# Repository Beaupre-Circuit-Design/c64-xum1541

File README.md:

# C64-XUM1541

# Introduction

This project is a collections of 3 subprojects, XUM1541, an OpenCBM compatible interface, a VIA adapter to add a parallel interface to a 1541 (SpeedDos and XUM1541 Compatible) and a C64 User Port adapter for the paralle interface (SpeedDos compatible).

If the only thing you need is to backup and restore your floppies via a PC, only the XUM1541 is needed, with the optional VIA adapter if you want to make things a bit faster. The User Port adapter require a ROM upgrade for the C64 and the 1541 (which can be done with a ROM adapter like the [23xx Adapter](https://github.com/Beaupre-Circuit-Design/23xx-Adapter).

|Module           |PC |C64|SpeedDos|Description                                            |
|-----------------|---|---|--------|-------------------------------------------------------|
|[XUM1541](xum1541/)|Yes|N/A|N/A|Module for backing up and restoring floppies disk to PC|
|[VIA Adapter](xum1541-parallel-adapter/)|Optional|N/A|Required|Parallel interface for the 1541 disk drive|
|[User Port Adapter](xum1541-via-adapter)|N/A|N/A|Required|Parallel interface for the C64 user port|
|[23xx Adapter](https://github.com/Beaupre-Circuit-Design/23xx-Adapter)|N/A|N/A|Required|ROM adapter needed to install the SpeedDos Rom, needed to be done on both the C64 and the 1541|

See each project for build details.

# Licence

This work is licensed under the Creative Commons Attribution-NonCommercial-ShareAlike 4.0 International License. To view a copy of this license, visit http://creativecommons.org/licenses/by-nc-sa/4.0/ or send a letter to Creative Commons, PO Box 1866, Mountain View, CA 94042, USA.

# Revision History

|Revision  |Description                    |
|:--------:|-------------------------------|
|1.0       |Initial prototype              |
|2.0       |Add bank switching header      |

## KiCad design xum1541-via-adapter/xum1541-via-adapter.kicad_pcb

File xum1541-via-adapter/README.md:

# XUM1541 VIA Adapter

# Introduction

A SpeedDos compatible VIA Adapter for the 1541 disk drive to enable parallel communication.

# Components and assembly

Component selection isn't terribly critical, whathever you have in hand that fit the values will probably work just fine. Values for the led resistors will drive them at around 18ma which may be quite bright, increase the values if it's the case.

As alway, when assembling, start with the smallest components and grow in size as you go.

|Qty|Ref|Value|Description|
|---|---|-----|-----------|
|2|U1A|Conn_01x20|20 pin 2.54mm Round Male Connector Single Row|
|1|U1B|Conn_02x06_Odd_Even|Shrouded Square Pins 2.5mm 6mm 2x6 Pin Headers Righ Angle|

# Licence

This work is licensed under the Creative Commons Attribution-NonCommercial-ShareAlike 4.0 International License. To view a copy of this license, visit http://creativecommons.org/licenses/by-nc-sa/4.0/ or send a letter to Creative Commons, PO Box 1866, Mountain View, CA 94042, USA.

# Revision History

|Revision  |Description                    |
|:--------:|-------------------------------|
|1.0       |Initial prototype              |

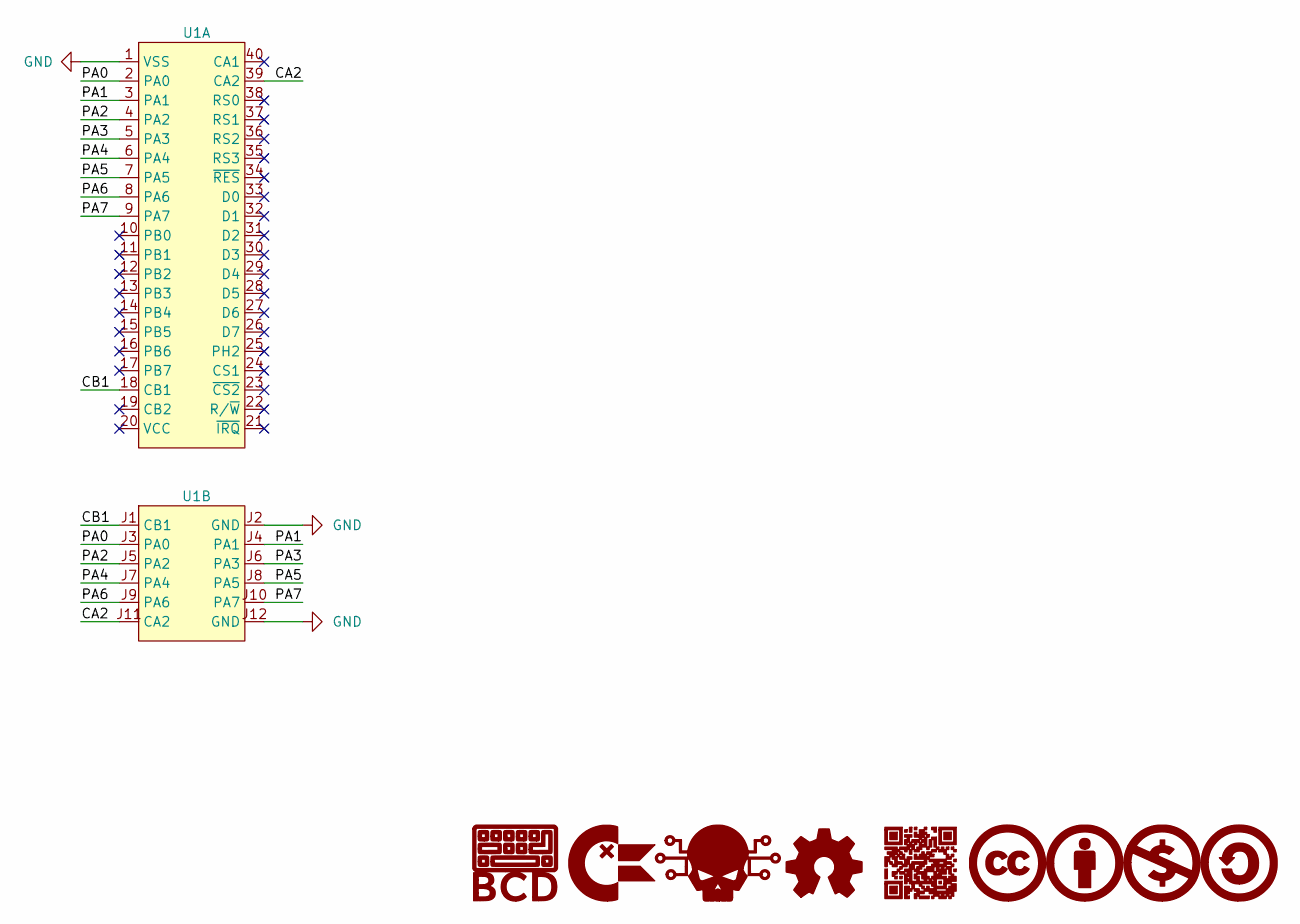
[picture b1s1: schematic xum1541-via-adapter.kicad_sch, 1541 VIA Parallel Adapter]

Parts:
G1: BCD_Logo; BCD_Logo_5mm
G2: ChickenLips; ChickenLips_2.5mm
G3: Skull; Skull_2.5mm
G4: OpenSource_Hardware; Open_Source_Hardware_2.5mm
G5: CreativeCommons; CreativeCommons_2.5mm
G6: CreativeCommons_Attribution; CreativeCommons_Attribution_2.5mm
G7: CreativeCommons_NonCommercial; CreativeCommons_NonCommercial_2.5mm
G8: CreativeCommons_ShareAlike; CreativeCommons_ShareAlike_2.5mm
G9: BDC_QR; BDC_QR_5mm
U1: MCS6522; MCS6522 Adapter

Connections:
/CA2: U1.39 (CA2), U1.J11 (CA2)
/CB1: U1.18 (CB1), U1.J1 (CB1)
/PA0: U1.2 (PA0), U1.J3 (PA0)
/PA1: U1.3 (PA1), U1.J4 (PA1)
/PA2: U1.4 (PA2), U1.J5 (PA2)
/PA3: U1.5 (PA3), U1.J6 (PA3)
/PA4: U1.6 (PA4), U1.J7 (PA4)
/PA5: U1.7 (PA5), U1.J8 (PA5)
/PA6: U1.8 (PA6), U1.J9 (PA6)
/PA7: U1.9 (PA7), U1.J10 (PA7)
GND: U1.1 (VSS), U1.J2 (GND), U1.J12 (GND)

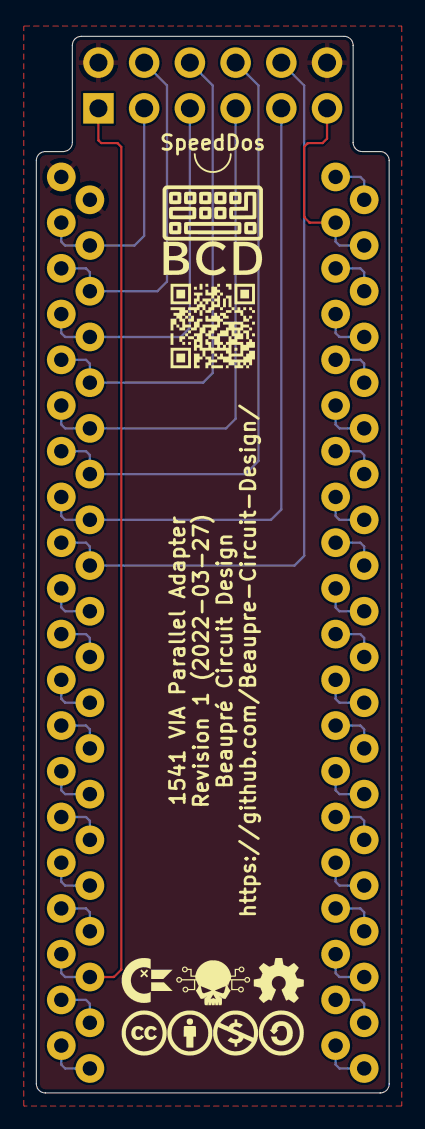
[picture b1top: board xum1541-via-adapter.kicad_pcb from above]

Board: 2 copper layers, 19.6 x 58.7 mm, 10 parts (0 on the bottom side), 11 nets.

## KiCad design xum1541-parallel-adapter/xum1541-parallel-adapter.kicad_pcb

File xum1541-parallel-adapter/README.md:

# XUM1541 Parallel Adapter

# Introduction

A SpeedDos compatible interface for the 1541 disk drive to enable parallel communication.

# Components and assembly

Component selection isn't terribly critical, whathever you have in hand that fit the values will probably work just fine. Values for the led resistors will drive them at around 18ma which may be quite bright, increase the values if it's the case.

As alway, when assembling, start with the smallest components and grow in size as you go.

|Qty|Ref|Value|Description|
|---|---|-----|-----------|
|1|D1|Red Led|Light Emitting Diodes Red Diffused 5mm 20mA/1.9V|
|1|R1|180Ω|Resistors 180Ω Axial Leaded Through Hole|
|1|SW1|SW_Push|Micro-Switch 6x6mm|
|1|UP1|C64 User Port|24 Pins 805 Series 3.96mm Pitch PCB Slot Solder Card Edge Connector|

# Licence

This work is licensed under the Creative Commons Attribution-NonCommercial-ShareAlike 4.0 International License. To view a copy of this license, visit http://creativecommons.org/licenses/by-nc-sa/4.0/ or send a letter to Creative Commons, PO Box 1866, Mountain View, CA 94042, USA.

# Revision History

|Revision  |Description                    |
|:--------:|-------------------------------|
|1.0       |Initial prototype              |

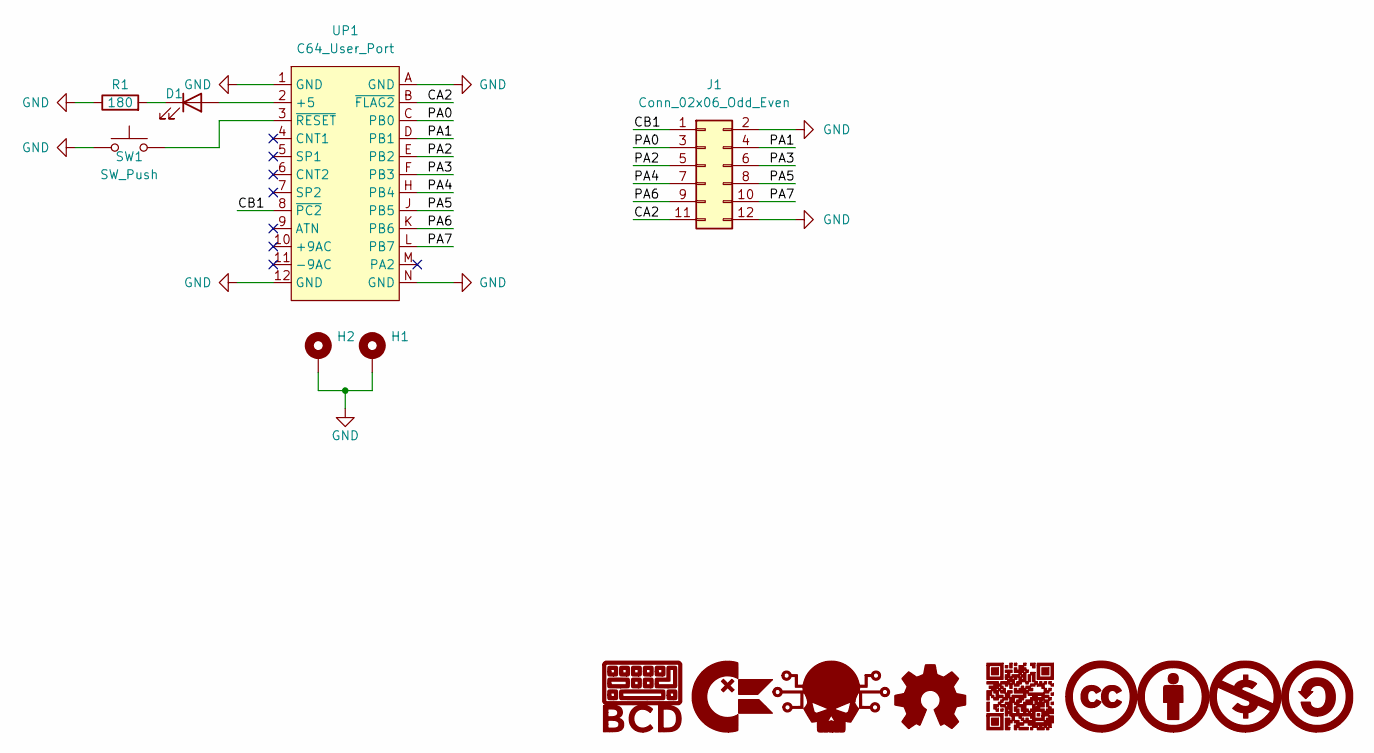
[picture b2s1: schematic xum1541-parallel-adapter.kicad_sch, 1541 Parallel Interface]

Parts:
D1: LED; LED_D5.0mm; Mfr.Part L-513ID; LCSC C2895168
G1: BCD_Logo; BCD_Logo_5mm
G2: ChickenLips; ChickenLips_2.5mm
G3: Skull; Skull_2.5mm
G4: OpenSource_Hardware; Open_Source_Hardware_2.5mm
G5: CreativeCommons; CreativeCommons_2.5mm
G6: CreativeCommons_Attribution; CreativeCommons_Attribution_2.5mm
G7: CreativeCommons_NonCommercial; CreativeCommons_NonCommercial_2.5mm
G8: CreativeCommons_ShareAlike; CreativeCommons_ShareAlike_2.5mm
G9: BDC_QR; BDC_QR_5mm
H1, H2: MountingHole_Pad; MountingHole_3.2mm_M3_Pad
J1: Conn_02x06_Odd_Even; PinHeader_2x06_P2.54mm_Horizontal; Mfr.Part PZ254R-12-12P; LCSC C492434
R1: 180; R_Axial_DIN0207_L6.3mm_D2.5mm_P10.16mm_Horizontal; Mfr.Part MFR0W4F1800A50; LCSC C58665
SW1: SW_Push; SW_PUSH_6mm_H4.3mm
UP1: C64_User_Port; C64 User Port

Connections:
/CA2: J1.11, UP1.B (~FLAG2)
/CB1: J1.1, UP1.8 (~PC2)
/PA0: J1.3, UP1.C (PB0)
/PA1: J1.4, UP1.D (PB1)
/PA2: J1.5, UP1.E (PB2)
/PA3: J1.6, UP1.F (PB3)
/PA4: J1.7, UP1.H (PB4)
/PA5: J1.8, UP1.J (PB5)
/PA6: J1.9, UP1.K (PB6)
/PA7: J1.10, UP1.L (PB7)
GND: H1.1, H2.1, J1.2, J1.12, R1.1, SW1.1, UP1.1 (GND), UP1.12 (GND), UP1.A (GND), UP1.N (GND)
unnamed: D1.1 (K), R1.2
unnamed: D1.2 (A), UP1.2 (+5)
unnamed: SW1.2, UP1.3 (~RESET)

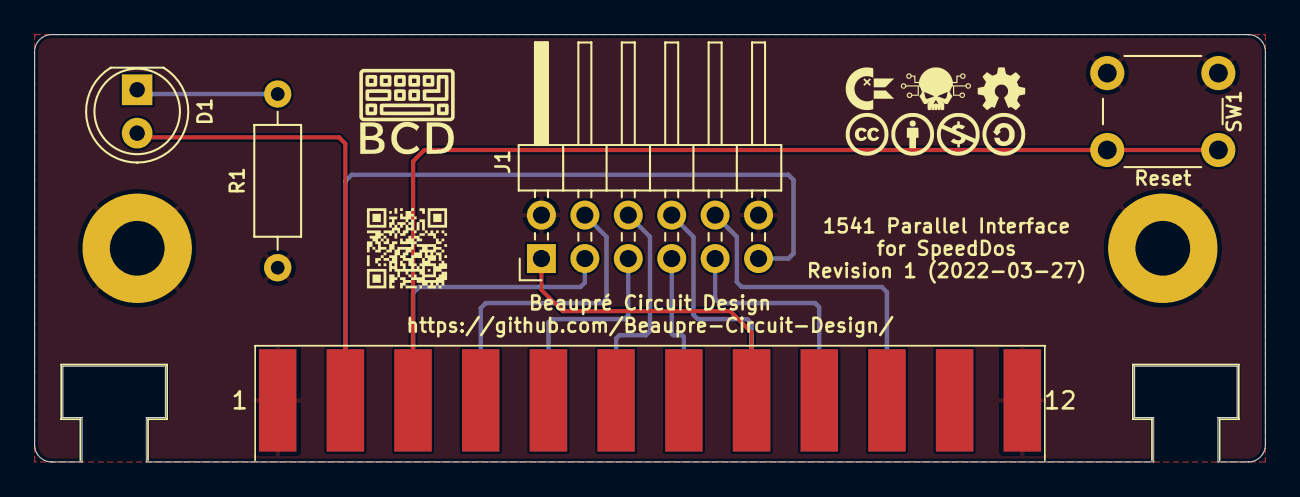
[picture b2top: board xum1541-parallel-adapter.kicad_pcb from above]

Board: 2 copper layers, 72.0 x 25.0 mm, 16 parts (0 on the bottom side), 14 nets.

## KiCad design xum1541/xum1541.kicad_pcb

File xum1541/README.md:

# XUM1541

# Introduction

An OpenCBM compatible interface for the 1541 disk drive that can be used to backup and restore floppies.

# Components and assembly

Component selection isn't terribly critical, whathever you have in hand that fit the values will probably work just fine. Values for the led resistors will drive them at around 18ma which may be quite bright, increase the values if it's the case. R1 to R5 can be anything between 1KΩ and 100KΩ. The decoupling capacitor C1 should be at least 10v or more.

As alway, when assembling, start with the smallest components (resistor and capacitor) and grow in size as you go.

|Qty|Ref|Value|Description|
|---|---|-----|-----------|
|1|C1|100nF|Ceramic Disc Capacitors 100nF 2.54mm Radial Leads (10v or more)|
|1|D1|Red Led|Light Emitting Diodes Red Diffused 5mm 20mA/1.9V|
|1|D2|Green Led|Light Emitting Diodes Green Diffused 5mm 20mA/2.2V|
|1|J1|Conn_02x06_Odd_Even|Pin Headers Righ Angle 2.54mm 2x6 Pin|
|1|J2|DIN-45322|6 pin Female DIN connector (240°) DIN 45322/60130-9 IEC-17|
|5|R1-R5|100kΩ|Resistors 100kΩ Axial Leaded Through Hole|
|1|R6|180Ω|Resistors 180Ω Axial Leaded Through Hole|
|1|R7|150Ω|Resistors 150Ω Axial Leaded Through Hole|
|1|SW1|SW_Push|Micro-Switch 6x6mm|
|1|U1|Arduino_Pro_Micro|SparkFun Arduino Pro Micro ATmega32U4|
|1|U2|74LS06|DIP-14 Inverters|

## Firmware

The firmware source code is available in the OpenCBM repository if you want to compile it yourself but since the code is stable and mature, it is not really needed and we can use a precompiled version. At the time of release, the current version is V08. 

Theses instructions are for Windows, but all the needed softwares are available for about any other platforms.

|Software|Local Link|Official Repository|
|--------|:----------:|:-----------:|
|Firmware|[xum1541-PROMICRO_7406-v08.hex](Firmware/xum1541-PROMICRO_7406-v08.hex)|[OpenCBM xum1541 Firmware](https://github.com/zyonee/opencbm/tree/master/xum1541)|
|WinAVR|N/A|[WinAVR Latest Release](https://sourceforge.net/projects/winavr/files/latest/download)|
|Zadig|N/A|[Zadig Latest Release](https://zadig.akeo.ie/)|
|OpenCBM|N/A|[OpenCBM Latest Release](https://spiro.trikaliotis.net/opencbm#download)|

Install WinAVR and open Device Manager, then connect the Arduino Pro Micro. A new Serial Port should appear after a few seconds.

This is the monitor serial port, but not the one we want, to put the Arduino into programming mode, reset it twice, you should see the Com Port number change, which tell you that we are in Firmware Update mode.

The Arduino will stay in this mode for about 8 seconds then revert back to the monitor serial port mode. So you need to be a little bit fast. First, note the Com Port number when the device is in Firmware Update mode (In this case, COM4), then open a command prompt and go to the bin directory of WinAVR. Once there, enter the following command but do not press enter (Adjust the path and filename of the firmware as needed):

~~~
avrdude -p m32u4 -c avr109 -P com4 -U flash:w:xum1541-PROMICRO_7406-v08.hex
~~~

Then, reset the Arduino twice to put it in programming mode and press enter. If everything goes well you should get a result like this:

~~~
C:\WinAVR-20100110\bin>avrdude -p m32u4 -c avr109 -P com4 -U flash:w:xum1541-PROMICRO_7406-v08.hex

Connecting to programmer: .
Found programmer: Id = "CATERIN"; type = S
    Software Version = 1.0; No Hardware Version given.
Programmer supports auto addr increment.
Programmer supports buffered memory access with buffersize=128 bytes.

Programmer supports the following devices:
    Device code: 0x44

avrdude: AVR device initialized and ready to accept instructions

Reading | ################################################## | 100% 0.00s

avrdude: Device signature = 0x1e9587
avrdude: NOTE: FLASH memory has been specified, an erase cycle will be performed
         To disable this feature, specify the -D option.
avrdude: erasing chip
avrdude: reading input file "xum1541-PROMICRO_7406-v08.hex"
avrdude: input file xum1541-PROMICRO_7406-v08.hex auto detected as Intel Hex
avrdude: writing flash (9026 bytes):

Writing | ################################################## | 100% 1.29s

avrdude: 9026 bytes of flash written
avrdude: verifying flash memory against xum1541-PROMICRO_7406-v08.hex:
avrdude: load data flash data from input file xum1541-PROMICRO_7406-v08.hex:
avrdude: input file xum1541-PROMICRO_7406-v08.hex auto detected as Intel Hex
avrdude: input file xum1541-PROMICRO_7406-v08.hex contains 9026 bytes
avrdude: reading on-chip flash data:

Reading | ################################################## | 100% 0.41s

avrdude: verifying ...
avrdude: 9026 bytes of flash verified

avrdude: safemode: Fuses OK

avrdude done.  Thank you.

C:\WinAVR-20100110\bin>
~~~

The Arduino will reset after the Firmware Upload and a new device should appear in device manager:

## Driver installation

Next, we need to install the driver for the new device, start **Zadig** and select the **xum1541 floppy adapter (PROMICRO_7406)** device, next change the driver to **libusp-win32**, finally click **Install Driver** and wait for the confirmation message.

## OpenCBM Installation

Unzip OpenCBM into a temporary directory and open a **Command Prompt** in **Administrator** mode, switch to the temporary OpenCBM directory and type the following command:

~~~
install.cmd xum1541
~~~

Install will start, check for a previous installation and advice that it will request elevated privileges, press any key to start installation or CTRL-C to abort.

~~~
find: /i: No such file or directory
OpenCBM installation script
===========================

Elevating privileges in order to install OpenCBM.
Please grant the rights on the UAC prompt,
or I will not be able to continue

Your installation will continue in another window.
Press any key to continue . . .
~~~

Another window will open and installation will continue, when it ask to install drivers, answer no since they have already been install.

~~~
Continuing...
24 File(s) copied
5 File(s) copied
2 File(s) copied
3 File(s) copied
Working directory = 'C:\Program Files\opencbm\',
system  directory = 'C:\Windows\system32\',
driver  directory = 'C:\Windows\system32\DRIVERS\'.
Using plugin: 'xum1541' with filename 'opencbm-xum1541.dll'.
++++ Install: 'xum1541' with filename 'opencbm-xum1541.dll'.
Copying '.\opencbm-xum1541.dll' to 'C:\Windows\system32\opencbm-xum1541.dll'

=================================================
=== OpenCBM v0.4.99.104 for  xum1541
=== installation done
===
=== Add C:\Program Files\opencbm to your PATH to use the command line tools there.
=================================================

I could install the necessary USB drivers if you like.
If you want this, then please
1. attach your device, and then
2. answer the following question with "y", without parenthesis:

Do you want me to install the necessary USB drivers for you? (y/n) n
NO.

That's it, I am finished.
Press any key to continue . . .
~~~

## Testing

First, test without connecting anything, open an OpenCBM Shell  and type the following command:

~~~
cbmctrl detect
~~~

You should get the following error:

~~~
C:\Users\xum1541>cbmctrl detect
error: no xum1541 device found
An error occurred opening OpenCBM, aborting...

C:\Users\xum1541>
~~~

Next, connect the XUM1541 but do not connect a drive to it and try the command again, this time your should not see any output. This confirm that the XUM1541 is detected and working correctly.

~~~
C:\Users\xum1541>cbmctrl detect

C:\Users\xum1541>
~~~

Finally, disconnect the XUM1541 from the computer and make sure the 1541 is powered off, connect the 1541 to the XUM1541 with the IEC Cable, connect the XUM1541 to the computer and finally turn on the 1541. You may now try the command again, and this time you should see the device ID and model of the connected disk drive.

~~~
C:\Users\xum1541>cbmctrl detect
 8: 1541-II

C:\Users\xum1541>
~~~

## Basic OpenCBM commands

This is definitly not an exaustive guide, but just a few commands to test and do basic tasks.

### Reading disk directory

Reading the disk directory can be done with the **cbmctrl dir \<DISKID\>** command:

~~~
C:\Users\xum1541>cbmctrl dir 8
0 ."test/demo  1/85 " 84 2a
14   "how to use"       prg
8    "how part two"     prg
7    "how part three"   prg
4    "vic-20 wedge"     prg
1    "c-64 wedge"       prg
4    "dos 5.1"          prg
9    "printer test"     prg
6    "disk addr change" prg
12   "view bam"         prg
15   "display t&s"      prg
4    "check disk"       prg
11   "performance test" prg
5    "seq.file.demo"    prg
18   "rel.file.demo"    prg
7    "sd.backup.c16"    prg
7    "sd.backup.plus4"  prg
10   "sd.backup.c64"    prg
7    "print.64.util"    prg
7    "print.c16.util"   prg
7    "print.+4.util"    prg
13   "uni-copy"         prg
30   "c64 basic demo"   prg
35   "+4 basic demo"    prg
8    "load address"     prg
7    "unscratch"        prg
5    "header change"    prg
403 blocks free.
00, ok,00,00

C:\Users\xum1541>
~~~

### Backing up disk to PC or restore to disk from PC

Making backup or restoring a disk can be done with the **d64copy \<SRC\> \<DST\>** command:

Backup disk in drive id **8** to disk image **1541-demo.d64**:
~~~
C:\Users\xum1541>d64copy 8 1541-demo.d64
[Warning] growing image file to 683 blocks
 1: *********************
 2: *********************
 3: *********************
 4: *********************
 5: *********************
 6: *********************
 7: *********************
 8: *********************
 9: *********************
10: *********************
11: *********************
12: *********************
13: *********************
14: *********************
15: *********************
16: *********************
17: *********************
18: *******************
19: *******************
20: *******************
21: *******************
22: *******************
23: *******************
24: *******************
25: ******************
26: ******************
27: ******************
28: ******************
29: ******************
30: ******************
31: *****************
32: *****************
33: *****************
34: *****************
35: *****************       100%   683/683
683 blocks copied.

C:\Users\xum1541>
~~~

Restore disk image **1541-demo.d64** to disk in drive id **8**:

~~~
C:\Users\xum1541>d64copy 1541-demo.d64 8
 1: *********************
 2: *********************
 3: *********************
 4: *********************
 5: *********************
 6: *********************
 7: *********************
 8: *********************
 9: *********************
10: *********************
11: *********************
12: *********************
13: *********************
14: *********************
15: *********************
16: *********************
17: *********************
18: *******************
19: *******************
20: *******************
21: *******************
22: *******************
23: *******************
24: *******************
25: ******************
26: ******************
27: ******************
28: ******************
29: ******************
30: ******************
31: *****************
32: *****************
33: *****************
34: *****************
35: *****************       100%   683/683
683 blocks copied.

C:\Users\xum1541>
~~~

### Format a disk

Format a disk in drive id **8**:

~~~
C:\Users\xum1541>cbmformat 8 XUM1541_FORMAT,01 -c

C:\Users\xum1541>cbmctrl dir 8
0 ."xum1541⌂format  " 01 2a
664 blocks free.
00, ok,00,00

C:\Users\xum1541>
~~~

For more information, see the official [OpenCBM](https://opencbm.trikaliotis.net/) documentation.

# Licence

This work is licensed under the Creative Commons Attribution-NonCommercial-ShareAlike 4.0 International License. To view a copy of this license, visit http://creativecommons.org/licenses/by-nc-sa/4.0/ or send a letter to Creative Commons, PO Box 1866, Mountain View, CA 94042, USA.

# Revision History

|Revision  |Description                    |
|:--------:|-------------------------------|
|1.0       |Initial prototype              |

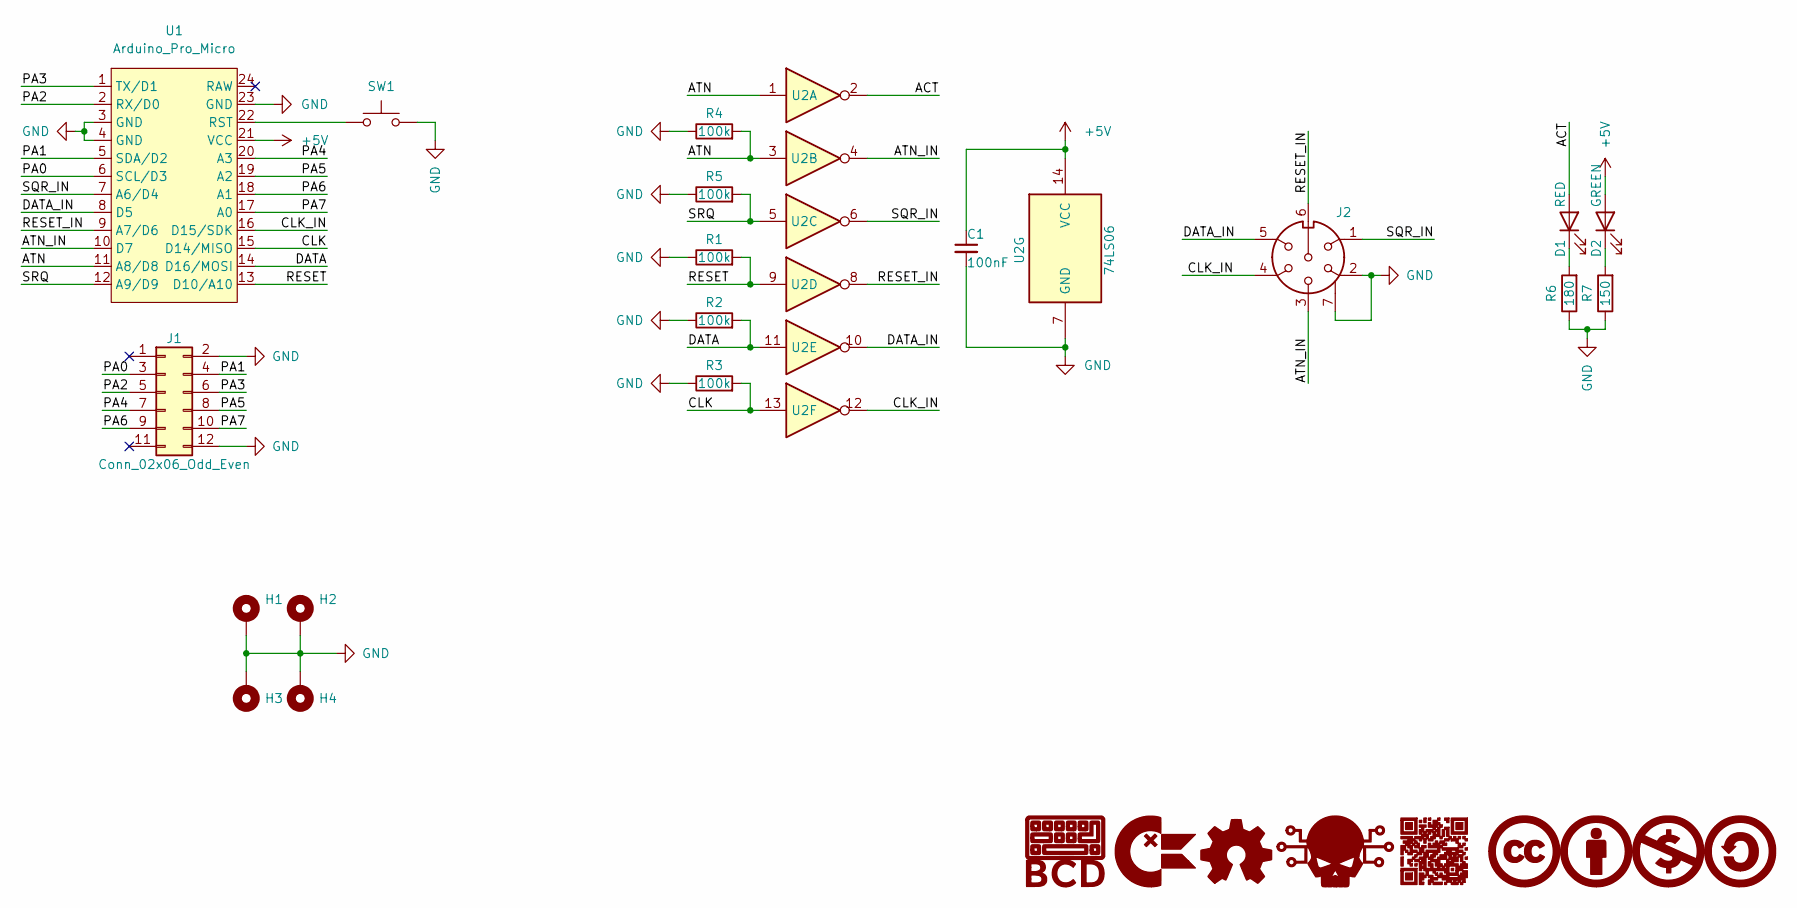
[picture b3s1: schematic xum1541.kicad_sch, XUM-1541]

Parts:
C1: 100nF; C_Disc_D5.0mm_W2.5mm_P2.50mm; Mfr.Part CC1H104ZA1PD3F5P3003; LCSC C353903
D1: RED; LED_D5.0mm; Mfr.Part L-513ID; LCSC C2895168
D2: GREEN; LED_D5.0mm; Mfr.Part L-513GD; LCSC C2895169
G1: BCD_Logo; BCD_Logo_5mm
G2: ChickenLips; ChickenLips_5mm
G3: OpenSource_Hardware; Open_Source_Hardware_5mm
G4: Skull; Skull_5mm
G5: CreativeCommons; CreativeCommons_5mm
G6: CreativeCommons_Attribution; CreativeCommons_Attribution_5mm
G7: CreativeCommons_NonCommercial; CreativeCommons_NonCommercial_5mm
G8: CreativeCommons_ShareAlike; CreativeCommons_ShareAlike_5mm
G9: BDC_QR; BDC_QR_10mm
H1, H2, H3, H4: MountingHole_Pad; MountingHole_2.7mm_Pad_TopBottom
J1: Conn_02x06_Odd_Even; PinHeader_2x06_P2.54mm_Horizontal; Mfr.Part PZ254R-12-12P; LCSC C492434
J2: DIN-45322; DIN_45322
R1, R2, R3, R4, R5: 100k; R_Axial_DIN0207_L6.3mm_D2.5mm_P2.54mm_Vertical; Mfr.Part MFR0W4F1003A50; LCSC C58597
R6: 180; R_Axial_DIN0207_L6.3mm_D2.5mm_P2.54mm_Vertical; Mfr.Part MFR0W4F1800A50; LCSC C58665
R7: 150; R_Axial_DIN0207_L6.3mm_D2.5mm_P2.54mm_Vertical; Mfr.Part MFR0W4F1500A50; LCSC C58668
SW1: SW_Push; SW_PUSH_6mm
U1: Arduino_Pro_Micro; Mfr.Part DEV-12640
U2: 74LS06; DIP-14_W7.62mm_Socket; Mfr.Part SN74LS06N; LCSC C21803

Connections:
+5V: C1.1, D2.2 (A), U1.21 (VCC), U2.14 (VCC)
/ACT: D1.2 (A), U2.2
/ATN: R4.2, U1.11 (A8/D8), U2.1, U2.3
/ATN_IN: J2.3, U1.10 (D7), U2.4
/CLK: R3.2, U1.15 (D14/MISO), U2.13
/CLK_IN: J2.4, U1.16 (D15/SDK), U2.12
/DATA: R2.2, U1.14 (D16/MOSI), U2.11
/DATA_IN: J2.5, U1.8 (D5), U2.10
/PA0: J1.3, U1.6 (SCL/D3)
/PA1: J1.4, U1.5 (SDA/D2)
/PA2: J1.5, U1.2 (RX/D0)
/PA3: J1.6, U1.1 (TX/D1)
/PA4: J1.7, U1.20 (A3)
/PA5: J1.8, U1.19 (A2)
/PA6: J1.9, U1.18 (A1)
/PA7: J1.10, U1.17 (A0)
/RESET: R1.2, U1.13 (D10/A10), U2.9
/RESET_IN: J2.6, U1.9 (A7/D6), U2.8
/SQR_IN: J2.1, U1.7 (A6/D4), U2.6
/SRQ: R5.2, U1.12 (A9/D9), U2.5
GND: C1.2, H1.1, H2.1, H3.1, H4.1, J1.2, J1.12, J2.2, J2.7, R1.1, R2.1, R3.1, R4.1, R5.1, R6.1, R7.1, SW1.2, U1.3 (GND), U1.4 (GND), U1.23 (GND), U2.7 (GND)
unnamed: D1.1 (K), R6.2
unnamed: D2.1 (K), R7.2
unnamed: SW1.1, U1.22 (RST)

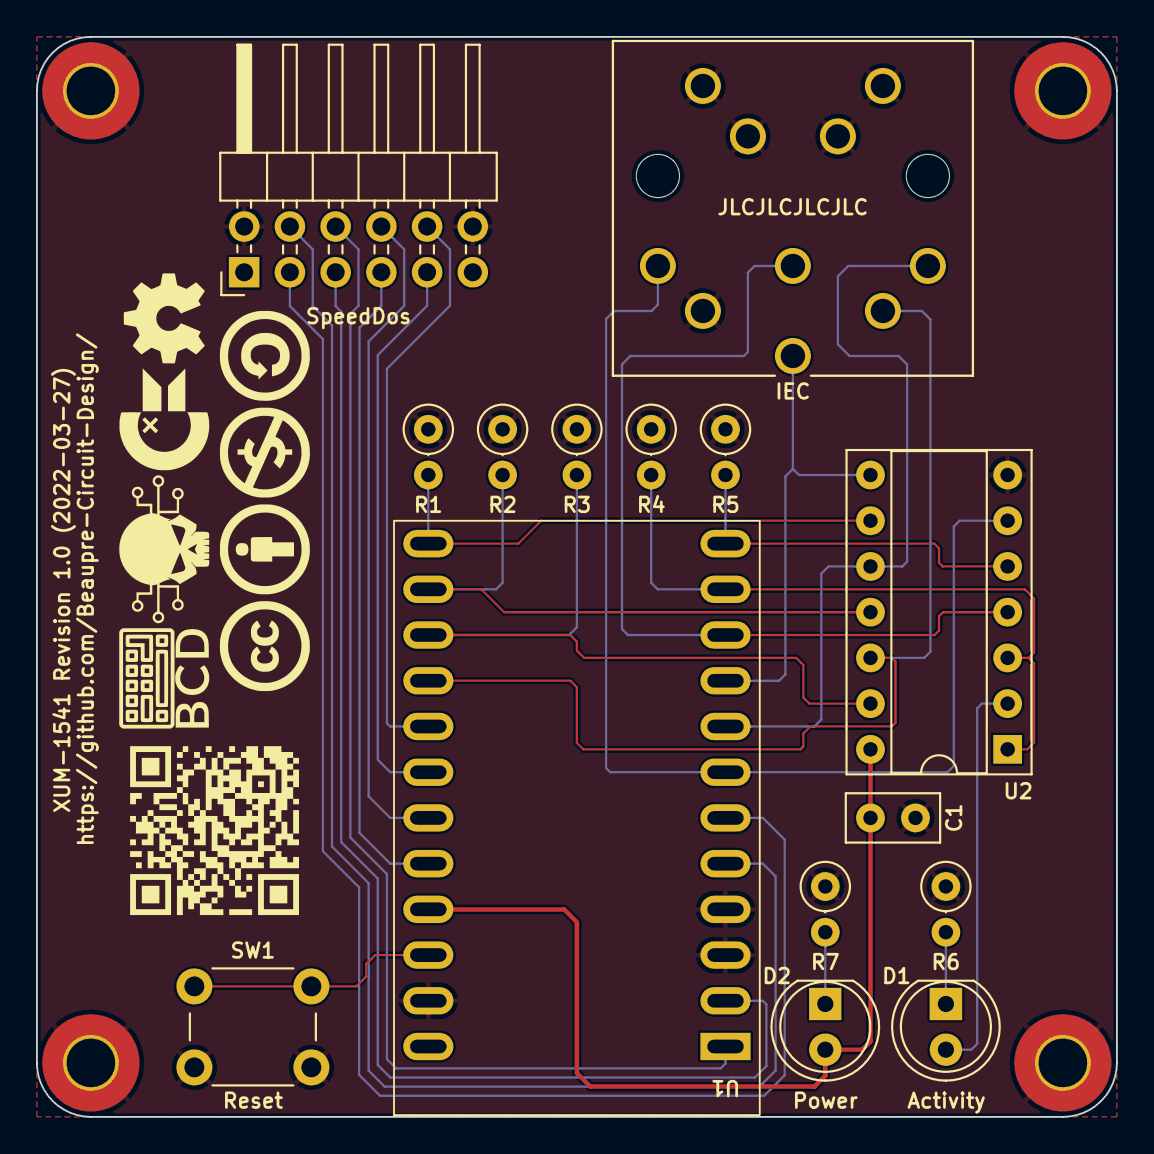
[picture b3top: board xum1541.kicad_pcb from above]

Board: 2 copper layers, 60.0 x 60.0 mm, 28 parts (0 on the bottom side), 24 nets.

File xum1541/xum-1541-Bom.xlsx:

Ref | Value | Description | Footprint | Datasheet | Manufacturer | Mfr.Part | LCSC | AliExpress | Notes
C1 | 100nF | Ceramic Disc Capacitors 100nF -20%~+80% Y5V 2.54mm 50V Radial Leaded | Capacitor_THT:C_Disc_D5.0mm_W2.5mm_P2.50mm | https://datasheet.lcsc.com/lcsc/2110081130_Dersonic-CC1H104Z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 | Dersonic | CC1H104ZA1PD3F5P3003 | C353903
D1 | RED | Light Emitting Diodes Red Diffused 5mm 20mA/1.9V | LED_THT:LED_D5.0mm | https://datasheet.lcsc.com/lcsc/2109251830_PARALIGHT-L-513ID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 | PARALIGHT | L-513ID | C2895168
D2 | GREEN | Light Emitting Diodes Green Diffused 5mm 20mA/2.2V | LED_THT:LED_D5.0mm | https://datasheet.lcsc.com/lcsc/2109251830_PARALIGHT-L-513GD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 | PARALIGHT | L-513GD | C2895169
J1 | Conn_02x06_Odd_Even | Shrouded Square Pins 2.5mm 6mm 2x6 Pin Headers Righ Angle | Connector_PinHeader_2.54mm:PinHeader_2x06_P2.54mm_Horizontal | https://datasheet.lcsc.com/lcsc/2003091512_XFCN-PZ254R-12-12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 | XFCN | PZ254R-12-12P | C492434
J2 | DIN-45322 | 6 pin (240°) DIN 45322/60130-9 IEC-17 | DIN_45322:DIN_45322 | https://www.aliexpress.com/item/1005001265863686.html |  |  |  | 1005001265863686
R1 | 100k | Metal Film Resistors 100kΩ ±1% 250mW ±50ppm/℃ Axial Leaded Through Hole Resisto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 | Resistor_THT:R_Axial_DIN0207_L6.3mm_D2.5mm_P2.54mm_Vertical | https://datasheet.lcsc.com/lcsc/1810161350_UNI-ROYAL-Uniroya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 | Uniroyal Elec | MFR0W4F1003A50 | C58597
R2 | 100k | Metal Film Resistors 100kΩ ±1% 250mW ±50ppm/℃ Axial Leaded Through Hole Resisto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 | Resistor_THT:R_Axial_DIN0207_L6.3mm_D2.5mm_P2.54mm_Vertical | https://datasheet.lcsc.com/lcsc/1810161350_UNI-ROYAL-Uniroya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 | Uniroyal Elec | MFR0W4F1003A50 | C58597
R3 | 100k | Metal Film Resistors 100kΩ ±1% 250mW ±50ppm/℃ Axial Leaded Through Hole Resisto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 | Resistor_THT:R_Axial_DIN0207_L6.3mm_D2.5mm_P2.54mm_Vertical | https://datasheet.lcsc.com/lcsc/1810161350_UNI-ROYAL-Uniroya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 | Uniroyal Elec | MFR0W4F1003A50 | C58597
R4 | 100k | Metal Film Resistors 100kΩ ±1% 250mW ±50ppm/℃ Axial Leaded Through Hole Resisto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 | Resistor_THT:R_Axial_DIN0207_L6.3mm_D2.5mm_P2.54mm_Vertical | https://datasheet.lcsc.com/lcsc/1810161350_UNI-ROYAL-Uniroya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 | Uniroyal Elec | MFR0W4F1003A50 | C58597
R5 | 100k | Metal Film Resistors 100kΩ ±1% 250mW ±50ppm/℃ Axial Leaded Through Hole Resisto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 | Resistor_THT:R_Axial_DIN0207_L6.3mm_D2.5mm_P2.54mm_Vertical | https://datasheet.lcsc.com/lcsc/1810161350_UNI-ROYAL-Uniroya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 | Uniroyal Elec | MFR0W4F1003A50 | C58597
R6 | 180 | Metal Film Resistors 180Ω ±1% 250mW ±50ppm/℃ Axial Leaded Through Hole Resistors | Resistor_THT:R_Axial_DIN0207_L6.3mm_D2.5mm_P2.54mm_Vertical | https://datasheet.lcsc.com/lcsc/1810161317_UNI-ROYAL-Uniroya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 | Uniroyal Elec | MFR0W4F1800A50 | C58665
R7 | 150 | Metal Film Resistors 150Ω ±1% 250mW ±50ppm/℃ Axial Leaded Through Hole Resistors | Resistor_THT:R_Axial_DIN0207_L6.3mm_D2.5mm_P2.54mm_Vertical | https://datasheet.lcsc.com/lcsc/1810271810_UNI-ROYAL-Uniroya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 | Uniroyal Elec | MFR0W4F1500A50 | C58668
SW1 | SW_Push | Micro-Switch 6x6mm | Button_Switch_THT:SW_PUSH_6mm | https://www.aliexpress.com/item/1005001806156574.html |  |  |  | 1005001806156574
U1 | Arduino_Pro_Micro | SparkFun Arduino Pro Micro ATmega32U4 | Arduino_Pro_Micro:Arduino_Pro_Micro | https://github.com/sparkfun/Pro_Micro | SparkFun | DEV-12640 |  | 32768308647
U2 | 74LS06 | DIP-14 Inverters | Package_DIP:DIP-14_W7.62mm_Socket | http://www.ti.com/lit/gpn/sn74LS06 | Texas Instruments | SN74LS06N | C21803
